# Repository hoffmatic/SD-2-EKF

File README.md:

# SD-2-EKF

Embedded-oriented estimator and airbrake-control scaffold for Project AMBAR.

The code now follows the AMBAR M5 report: a 3-inch test vehicle targeting
3000 ft apogee with +/-100 ft tolerance, autonomous airbrake deployment after
burnout, and live flight-state telemetry.

## What Is Implemented

- 4-state vertical EKF: altitude, vertical velocity, accelerometer bias, and
  barometer bias
- Timestamp validation for asynchronous IMU input
- Barometer innovation gating and Joseph-form covariance update
- Flight phase tracking: pad idle, boost, coast, airbrake active, recovery, fault
- Apogee prediction and bounded airbrake deployment command
- Embedded-friendly interfaces with fixed-size arrays and no heap allocation
- June 2 provisional KiCad pin-map constants in `include/ambar_board_pins.hpp`
- Datasheet-derived device IDs, bus modes, addresses, and register constants in
  `include/ambar_device_constants.hpp`
- Virtual sandboxes for flight behavior, electronics bring-up checks, and
  actuator motion/fault behavior
- RocketPy 1.12.1 trajectory physics using the M5-selected J420R thrust curve
  and a persistent bridge compiled from the production STM32 C estimator and
  flight-controller sources
- Deterministic timestamp/sensor fault injection, synthetic log replay, an
  older 200-trial 1-D safety sandbox, and a production-controller RocketPy
  campaign with per-run CSV output and seeded Latin-hypercube variation
- CTest regression tests and GitHub Actions verification

## Current Status

This is an integration scaffold, not flight-ready software.

The current production-STM32-C RocketPy cross-check fails: the nominal model
predicts 3829 ft AGL passive apogee versus 3379 ft in the June 14 M5 report and
only 42.7 ft/s off the reported 72-inch rail. Closed loop reaches 3327 ft AGL,
about 327 ft above target. These mismatches remain visible until the OpenRocket
configuration, mass properties, and drag data are reconciled.

Before use in flight hardware:

- Calibrate and hardware-qualify the existing sensor, radio, flash, USB, and
  TMC5240 driver paths
- Validate IMU mounting-axis selection, pad reference, and attitude limitations
- Final measured mass properties and drag curves for the RocketPy model
- Calibrate the existing drag-aware embedded predictor against final
  RocketPy/OpenRocket inputs and recorded tests
- Confirm TMC5240 current, speed, travel, homing, load, and fail-safe limits on
  the final mechanism
- Hardware-in-the-loop tests and recorded hardware-log replay
- Verify the existing telemetry/config/log packet paths against the GUI and
  ground station

## Build

If you are new to code or GitHub, start here:
[docs/beginner_quick_start.md](docs/beginner_quick_start.md).

Windows one-command sandbox runner:

```powershell
powershell -ExecutionPolicy Bypass -File .\scripts\run_sandboxes.ps1
```

RocketPy physics simulation:

```powershell
powershell -ExecutionPolicy Bypass -File .\scripts\run_rocketpy_sim.ps1
```

The first RocketPy run creates a local `.venv` and installs the pinned dependency.

Two baseline repeats plus 50 randomized closed-loop runs:

```powershell
powershell -ExecutionPolicy Bypass -File .\scripts\run_monte_carlo.ps1
```

You can also double-click `Run Monte Carlo Simulation.cmd`. Results are written
under `build\monte-carlo\<campaign-id>\`, including `runs.csv`, aggregate
metrics, sensitivity results, and representative profiles. See
[docs/monte_carlo_campaign.md](docs/monte_carlo_campaign.md).
`scripts/validate_monte_carlo_output.py` independently recomputes saved counts,
rates, distributions, joins, worst cases, and snapshot hashes.

Continuous RocketPy replay with one commanded three-rotation actuator sequence
per case is a separate, guarded HIL workflow:

```text
Build & Flash AMBAR Normal.cmd
Build & Flash AMBAR Continuous Test.cmd
Run Continuous HIL Test.cmd
```

The firmware build profile is an explicit flash boundary. `NORMAL` rejects
simulation, HIL override, and arbitrary bench-motion commands.
`CONTINUOUS_HIL` accepts USB trajectory replay and the separately labeled
forced `0 -> 153600 -> 0` TMC ramp-state sequence only after profile,
communications, driver, software-HOME, freshness, and arming checks pass. The
existing PCB is unchanged: PA0/PA1 remain LEDs, and target/`XACTUAL` are not
encoder or endpoint-switch evidence. The launcher requires the mechanism to be
manually fully closed before it declares software HOME once per process. Live evidence is
stored under `%LOCALAPPDATA%\AMBAR\TestRuns`, queried through SQLite, graphed
on a localhost dashboard, and exported to atomic CSV files. See
[docs/continuous_hil_testing.md](docs/continuous_hil_testing.md) and complete
[docs/continuous_hil_commissioning.md](docs/continuous_hil_commissioning.md)
before enabling motor power.

The separate `VARIABLE_HIL` profile closes RocketPy causally around the normal
fractional STM32 controller-to-actuator path and correlated TMC5240 `XACTUAL`
feedback. It rejects the forced FULL/HOME override used by `CONTINUOUS_HIL`,
requires an atomic versioned configuration readback before arming, and stores
hardware-safety and 3,000 ft performance verdicts independently. Because
`XACTUAL` is not an encoder, its results are labeled TMC ramp-state-coupled HIL.
See [docs/variable_hil_testing.md](docs/variable_hil_testing.md).

The guarded launcher is separate from the forced-stroke runner. It does not
open a COM port unless hardware mode, actuator motion, an explicit port, and a
software-HOME acknowledgement are all supplied:

```powershell
powershell -ExecutionPolicy Bypass -File .\scripts\run_variable_hil.ps1 `
  -Hardware -AllowActuatorMotion -Port COMx -Cycles 25
```

The launcher prompts for the exact word `CLOSED` before declaring software
HOME. Do not use the hardware command until the motor-off replay and staged
25/50/75/100% commissioning in the testing guide are complete.

Browser simulation console:

```powershell
powershell -ExecutionPolicy Bypass -File .\scripts\run_simulation_ui.ps1
```

The local dashboard provides Run All/Run Suite controls, adjustable RocketPy
trade-study inputs, scenario tables, interactive altitude/speed/acceleration/
deployment graphs, a production STM32-C phase timeline, CSV/JSON export, source-gap tracking,
and the complete raw terminal output. See
[docs/simulation_ui.md](docs/simulation_ui.md).

```powershell
cmake -S . -B build
cmake --build build
.\build\Debug\rocket_airbrake_ekf.exe
.\build\Debug\sim_flight_sandbox.exe
.\build\Debug\sim_electronics_sandbox.exe
.\build\Debug\sim_actuator_sandbox.exe
.\build\Debug\sim_fault_replay_sandbox.exe
.\build\Debug\sim_monte_carlo_sandbox.exe
.\build\Debug\ambar_core_tests.exe
.\build\Debug\ambar_controller_bridge.exe
.\build\Debug\ambar_stm32_controller_bridge.exe
```

For single-config generators, the executable may be under `build/rocket_airbrake_ekf`.
The sandbox executables may likewise be directly under `build/`.

Direct compiler check, useful on Windows when CMake is not installed:

```powershell
g++ -std=c++17 -Wall -Wextra -Wpedantic -I include src/ambar_airbrake.cpp src/main.cpp -o build\rocket_airbrake_ekf.exe
.\build\rocket_airbrake_ekf.exe
```

Direct sandbox checks:

```powershell
g++ -std=c++17 -Wall -Wextra -Wpedantic -I include src/ambar_airbrake.cpp sim/flight_sandbox.cpp -o build\sim_flight_sandbox.exe
g++ -std=c++17 -Wall -Wextra -Wpedantic -I include sim/electronics_sandbox.cpp -o build\sim_electronics_sandbox.exe
g++ -std=c++17 -Wall -Wextra -Wpedantic -I include sim/actuator_sandbox.cpp -o build\sim_actuator_sandbox.exe
.\build\sim_flight_sandbox.exe
.\build\sim_electronics_sandbox.exe
.\build\sim_actuator_sandbox.exe
```

## Legacy C++ Sensor Interface

The older native C++ scaffold expects vertical acceleration in the launch frame:

```cpp
flightComputer.updateImu(timestamp_s, verticalAcceleration_mps2);
```

The barometer update expects altitude above the launch pad:

```cpp
flightComputer.updateBarometer(barometerAltitudeAgl_m, barometerStdDev_m);
```

The production STM32 firmware instead consumes its configured, pad-referenced
IMU body-axis channel. The main RocketPy campaign now models that current
firmware contract, including attitude projection, while retaining world-vertical
truth as a separate diagnostic.

## Software Architecture

The repository retains an older shared C++ flight-logic scaffold for native
sandboxes. RocketPy and the new Monte Carlo campaign now use a separate bridge
compiled directly from the production STM32 `ambar_ekf.c` and `ambar_flight.c`
sources, preventing controller drift between the board and the main closed-loop
physics study. The browser UI launches programs and displays their reports; it
does not simulate the rocket itself.

See [docs/software_architecture.md](docs/software_architecture.md) for the data
flow, file dependency map, and the intended use case for each executable.

## Current Project Files

- [docs/project_requirements.md](docs/project_requirements.md): AMBAR M5
  requirements mapped to the estimator and controller.
- [docs/project_status.md](docs/project_status.md): implemented, simulated,
  provisional, and future capabilities with the current verification snapshot.
- [docs/hardware_map.md](docs/hardware_map.md): provisional June 2 V3 KiCad
  component and STM32 pin map, including routing maturity.
- [docs/datasheet_integration_notes.md](docs/datasheet_integration_notes.md):
  datasheet facts reflected in firmware constants.
- [docs/simulation_sandboxes.md](docs/simulation_sandboxes.md): project review
  summary and virtual sandbox instructions.
- [docs/simulation_ui.md](docs/simulation_ui.md): browser dashboard startup and
  controls.
- [docs/beginner_quick_start.md](docs/beginner_quick_start.md): plain-English
  instructions for downloading the repo and running the sandboxes on Windows.
- [docs/source_backed_simulation_inputs.md](docs/source_backed_simulation_inputs.md):
  values pulled from the M5 report/KiCad files versus values still treated as
  placeholders.
- [docs/m5_report_data_extract.md](docs/m5_report_data_extract.md): engineering
  values extracted from the June 14 M5 report, their confidence, and conflicts
  with older report material.
- [docs/sensor_architecture.md](docs/sensor_architecture.md): verified separation
  between the airbrake magnetometer and independent recovery GPS.
- [docs/software_architecture.md](docs/software_architecture.md): how the shared
  flight core, simulations, scripts, and browser UI connect.
- [docs/continuous_hil_testing.md](docs/continuous_hil_testing.md): firmware
  profiles, continuous supervisor, datasets, dashboard, and operator controls.
- [docs/continuous_hil_commissioning.md](docs/continuous_hil_commissioning.md):
  unchanged-PCB software-zero procedure, cutoff, staged motion, and 100-cycle
  qualification.
- [docs/variable_hil_testing.md](docs/variable_hil_testing.md): isolated causal
  variable-deployment profile, configuration handshake, timing fault rules,
  calibration gates, and staged 3,000 ft development campaign.
- [docs/simulation_audit.md](docs/simulation_audit.md): engineering review of
  what each simulation proves, current gaps, and recommended next simulations.
- [docs/m5_report_change_guide.md](docs/m5_report_change_guide.md):
  section-by-section advice for manually correcting the Word report.
- [firmware/stm32_airbrake_pcb](firmware/stm32_airbrake_pcb): STM32CubeIDE
  project copy for the Airbrake PCB, including the C EKF port, flash logging,
  radio command parsing, telemetry additions, and bench-gated actuator layer.
- [hardware/airbrake_pcb](hardware/airbrake_pcb): KiCad PCB project and local
  component libraries copied from the Airbrake PCB design folder.
- [hardware/datasheets](hardware/datasheets): local component datasheets used
  for firmware constants, bus assumptions, and safety notes.
- [firmware/rust_controller_reference](firmware/rust_controller_reference):
  standalone Rust controller reference copied from the local PCB folder.
- [tools/arduino_ide_shortcut](tools/arduino_ide_shortcut): readable extraction
  of the local Arduino IDE shortcut metadata.
- [tools/arduino_ground_receiver](tools/arduino_ground_receiver): Arduino/LILYGO
  SX1280 receiver sketch that decodes the STM32 binary EKF telemetry packets.

Older V2 screenshot notes and outdated BOM mismatch notes were removed from the
live repo so GitHub only presents the current working baseline.

## Safety Note

Rocket airbrake software can affect flight stability and recovery outcomes. Treat this
code as experimental until it has been validated with simulation, bench testing,
hardware-in-the-loop testing, and controlled flight data review.

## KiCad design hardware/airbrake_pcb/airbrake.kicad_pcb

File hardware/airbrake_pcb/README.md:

# Airbrake PCB KiCad Project

Source copied from:

```text
C:\Users\hoffm\OneDrive\Desktop\PCBs\PCB\Main Prefab Airbreak PCB\airbrake-PCB
```

This folder contains the live KiCad project files and local component libraries:

- `airbrake.kicad_pro`
- `airbrake.kicad_sch`
- `airbrake.kicad_pcb`
- `fp-lib-table`
- `sym-lib-table`
- `components/`

The local `.history` folder was not uploaded because it contains a nested Git
repository/history cache rather than the active PCB design files.

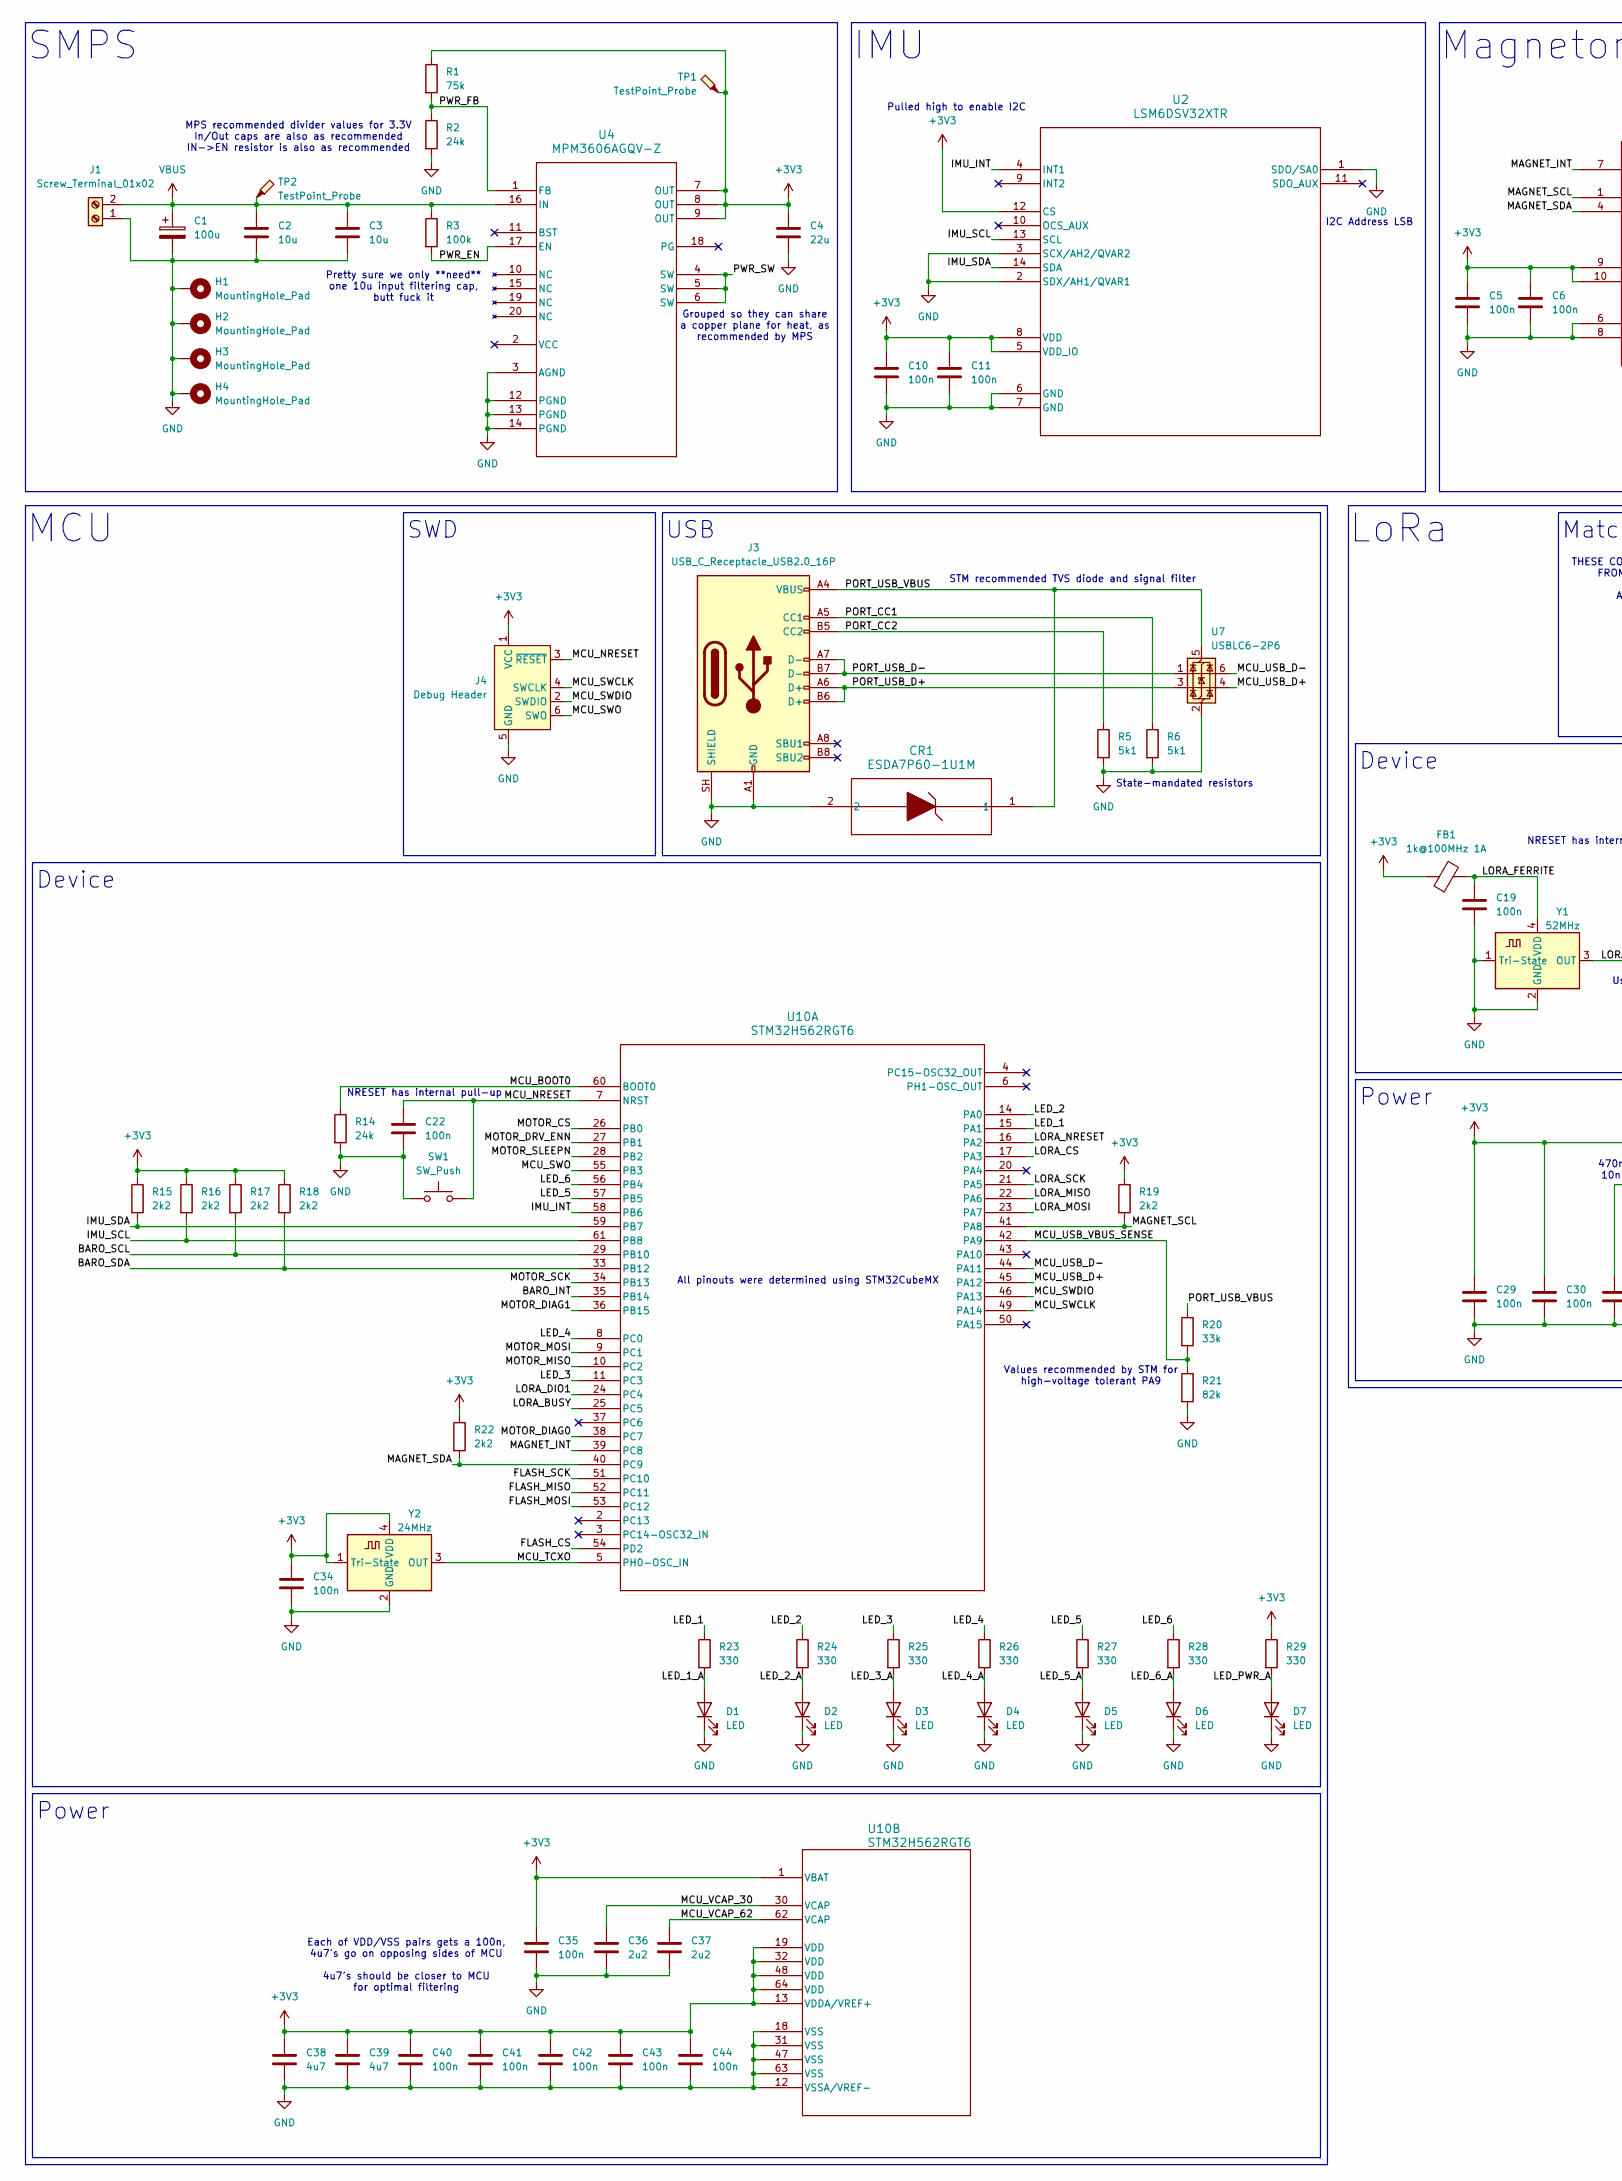
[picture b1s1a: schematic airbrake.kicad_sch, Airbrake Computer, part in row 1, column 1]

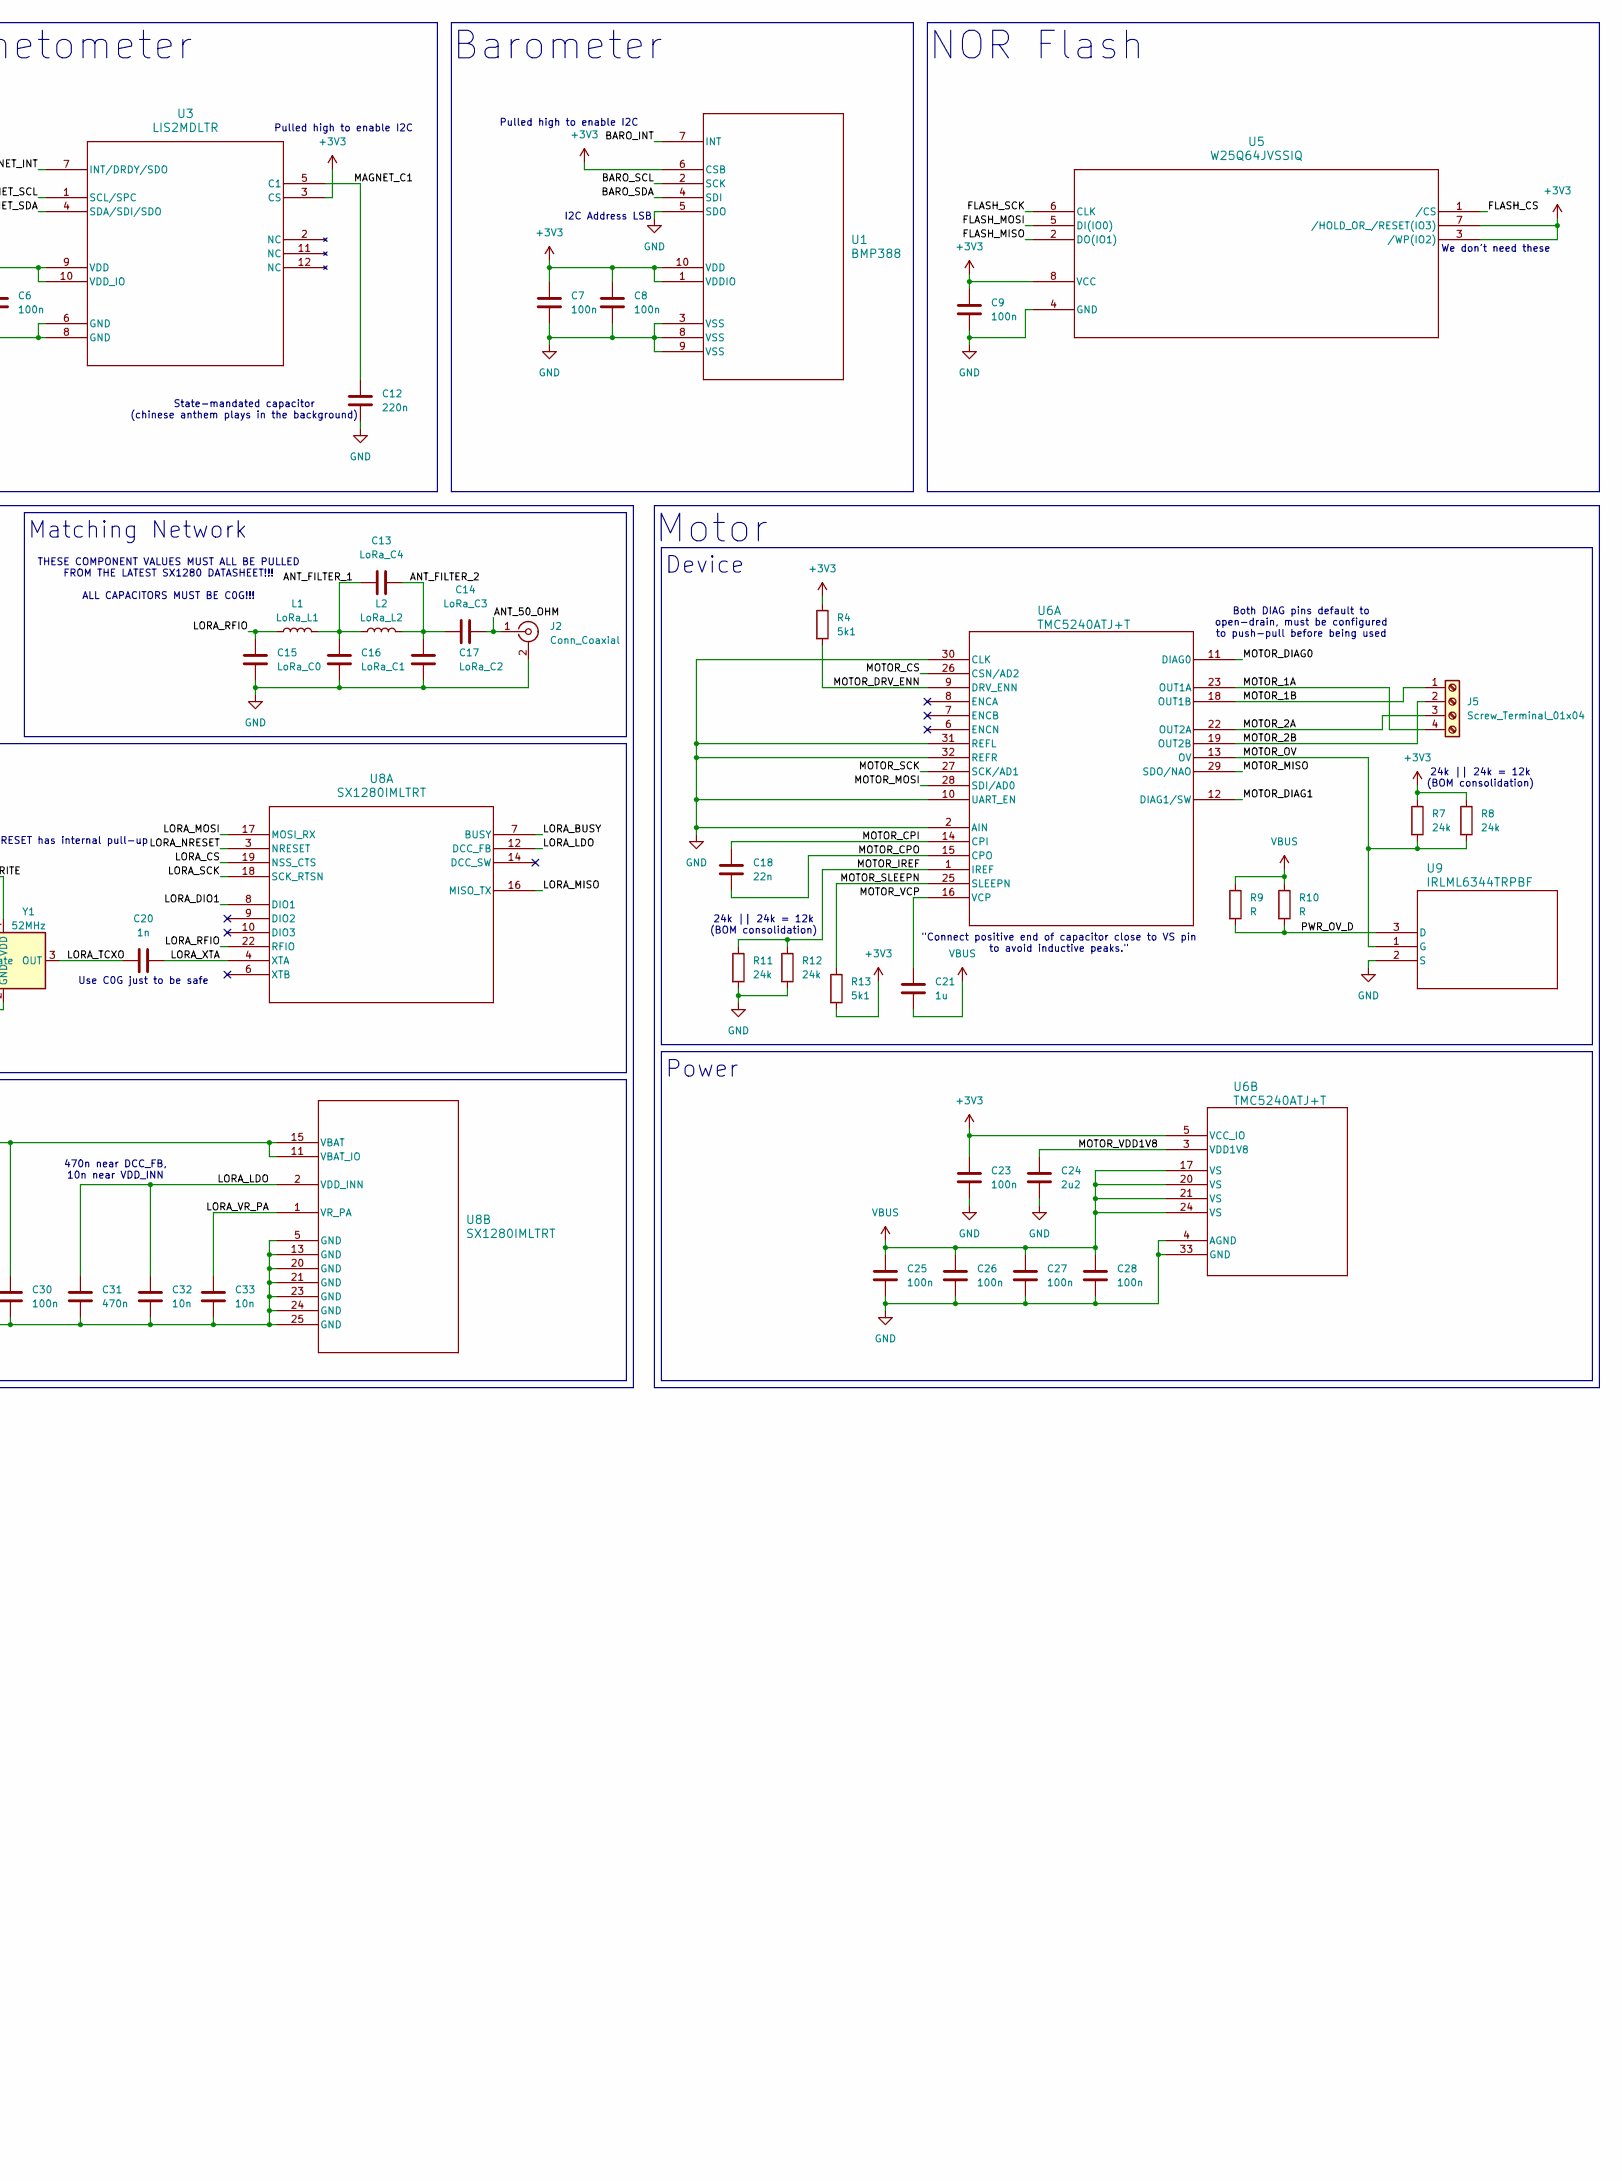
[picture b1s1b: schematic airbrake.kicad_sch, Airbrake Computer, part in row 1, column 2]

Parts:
C1: 100u; CP_Elec_6.3x7.7; LCSC part number C165974
C2, C3: 10u; C_0603_1608Metric; LCSC part number C194427
C4: 22u; C_0603_1608Metric; LCSC part number C29519229
C5, C6, C7, C8, C9, C10, C11, C19, C22, C23, C25, C26, C27, C28, C29, C30, C34, C35, C40, C41, C42, C43, C44: 100n; C_0402_1005Metric; LCSC part number C85858
C12: 220n; C_0402_1005Metric; LCSC part number C5159775
C13: LoRa_C4; C_0402_1005Metric; LCSC part number C76912
C14: LoRa_C3; C_0402_1005Metric; LCSC part number C2941926
C15: LoRa_C0; C_0402_1005Metric; LCSC part number C88902
C16: LoRa_C1; C_0402_1005Metric; LCSC part number C76899
C17: LoRa_C2; C_0402_1005Metric; LCSC part number C76899
C18: 22n; C_0402_1005Metric; LCSC part number C77023
C20: 1n; C_0402_1005Metric; LCSC part number C126493
C21: 1u; C_0402_1005Metric; LCSC part number C1518208
C24, C36, C37: 2u2; C_0402_1005Metric; LCSC part number C237392
C31: 470n; C_0402_1005Metric; LCSC part number C437527
C32, C33: 10n; C_0402_1005Metric; LCSC part number C91601
C38, C39: 4u7; C_0402_1005Metric; LCSC part number C2858031
CR1: ESDA7P60-1U1M; ZDO_1610_STM; LCSC part number C1975146
D1, D2, D3, D4, D5, D6, D7: LED; LED_0402_1005Metric; LCSC part number C25503856
FB1: 1k@100MHz 1A; L_0603_1608Metric; LCSC part number C160982
H1, H2, H3, H4: MountingHole_Pad; MountingHole_2.2mm_M2_Pad_Via
J1: Screw_Terminal_01x02; TerminalBlock_Xinya_XY308-2.54-2P_1x02_P2.54mm_Horizontal; LCSC part number C557685
J2: Conn_Coaxial; U.FL_Hirose_U.FL-R-SMT-1_Vertical; LCSC part number C88374
J3: USB_C_Receptacle_USB2.0_16P; USB_C_Receptacle_GCT_USB4105-xx-A_16P_TopMnt_Horizontal; LCSC part number C5184243
J4: Debug Header; Tag-Connect_TC2030-IDC-NL_2x03_P1.27mm_Vertical
J5: Screw_Terminal_01x04; TerminalBlock_Xinya_XY308-2.54-4P_1x04_P2.54mm_Horizontal; LCSC part number C915913
L1: LoRa_L1; L_0402_1005Metric; LCSC part number C2041661
L2: LoRa_L2; L_0402_1005Metric; LCSC part number C703121
R1: 75k; R_0402_1005Metric; LCSC part number C482299
R2, R7, R8, R11, R12, R14: 24k; R_0402_1005Metric; LCSC part number C295000
R3: 100k; R_0402_1005Metric; LCSC part number C481918
R4, R5, R6, R13: 5k1; R_0402_1005Metric; LCSC part number C2076825
R9, R10: R; R_2512_6332Metric_Pad1.40x3.35mm_HandSolder
R15, R16, R17, R18, R19, R22: 2k2; R_0402_1005Metric; LCSC part number C4202009
R20: 33k; R_0402_1005Metric; LCSC part number C482153
R21: 82k; R_0402_1005Metric; LCSC part number C482240
R23, R24, R25, R26, R27, R28, R29: 330; R_0402_1005Metric; LCSC part number C71626
SW1: SW_Push; SW_SPST_B3U-1000P; LCSC part number C231329
TP1, TP2: TestPoint_Probe; TestPoint_Pad_D2.5mm
U1: BMP388; QFN_BMP388_BOS; LCSC part number C779278
U2: LSM6DSV32XTR; LGA-14L_2p5X3p0X0p86_STM; LCSC part number C22461202
U3: LIS2MDLTR; LGA-12_2X2X1_STM; LCSC part number C919695
U4: MPM3606AGQV-Z; QFN3p0x5p0x1p6_MPM3606A_MNP; LCSC part number C7305220
U5: W25Q64JVSSIQ; SOIC-8_5P28X5P28_WIN-L; LCSC part number C179171
U6: TMC5240ATJ+T; 21-0140_T3255&plus_5C_ADI-L; LCSC part number C7494373
U7: USBLC6-2P6; SOT-666; LCSC part number C15999
U8: SX1280IMLTRT; QFN24_4X4_SEM-L; LCSC part number C125969
U9: IRLML6344TRPBF; IRLML6344TRPBF_INF
U10: STM32H562RGT6; LQFP64-10x10mm_STM; LCSC part number C19711662
Y1: 52MHz; Crystal_SMD_2016-4Pin_2.0x1.6mm; LCSC part number C22434896
Y2: 24MHz; Crystal_SMD_2520-4Pin_2.5x2.0mm; LCSC part number C2451215

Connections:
+3V3: C4.1, C5.1, C6.1, C7.1, C8.1, C9.1, C10.1, C11.1, C23.1, C29.1, C30.1, C34.1, C35.1, C38.1, C39.1, C40.1, C41.1, C42.1, C43.1, C44.1, FB1.1, J4.1 (VCC), R1.1, R4.1, R7.1, R8.1, R13.2, R15.1, R16.1, R17.1, R18.1, R19.1, R22.1, R29.1, TP1.1 (1_1), U1.1 (VDDIO), U1.6 (CSB), U1.10 (VDD), U2.5 (VDD_IO), U2.8 (VDD), U2.12 (CS), U3.3 (CS), U3.9 (VDD), U3.10 (VDD_IO), U4.7 (OUT), U4.8 (OUT), U4.9 (OUT), U5.3 (/WP(IO2)), U5.7 (/HOLD_OR_/RESET(IO3)), U5.8 (VCC), U6.5 (VCC_IO), U8.11 (VBAT_IO), U8.15 (VBAT), U10.1 (VBAT), U10.13 (VDDA/VREF+), U10.19 (VDD), U10.32 (VDD), U10.48 (VDD), U10.64 (VDD), Y2.1 (Tri-State), Y2.4 (VDD)
/ANT_50_OHM: C14.2, J2.1 (In)
/ANT_FILTER_1: C13.1, C16.1, L1.2, L2.1
/ANT_FILTER_2: C13.2, C14.1, C17.1, L2.2
/BARO_INT: U1.7 (INT), U10.35 (PB14)
/BARO_SCL: R17.2, U1.2 (SCK), U10.29 (PB10)
/BARO_SDA: R18.2, U1.4 (SDI), U10.33 (PB12)
/FLASH_CS: U5.1 (/CS), U10.54 (PD2)
/FLASH_MISO: U5.2 (DO(IO1)), U10.52 (PC11)
/FLASH_MOSI: U5.5 (DI(IO0)), U10.53 (PC12)
/FLASH_SCK: U5.6 (CLK), U10.51 (PC10)
/IMU_INT: U2.4 (INT1), U10.58 (PB6)
/IMU_SCL: R16.2, U2.13 (SCL), U10.61 (PB8)
/IMU_SDA: R15.2, U2.14 (SDA), U10.59 (PB7)
/LED_1: R23.1, U10.15 (PA1)
/LED_1_A: D1.2 (A), R23.2
/LED_2: R24.1, U10.14 (PA0)
/LED_2_A: D2.2 (A), R24.2
/LED_3: R25.1, U10.11 (PC3)
/LED_3_A: D3.2 (A), R25.2
/LED_4: R26.1, U10.8 (PC0)
/LED_4_A: D4.2 (A), R26.2
/LED_5: R27.1, U10.57 (PB5)
/LED_5_A: D5.2 (A), R27.2
/LED_6: R28.1, U10.56 (PB4)
/LED_6_A: D6.2 (A), R28.2
/LED_PWR_A: D7.2 (A), R29.2
/LORA_BUSY: U8.7 (BUSY), U10.25 (PC5)
/LORA_CS: U8.19 (NSS_CTS), U10.17 (PA3)
/LORA_DIO1: U8.8 (DIO1), U10.24 (PC4)
/LORA_FERRITE: C19.1, FB1.2, Y1.4 (VDD)
/LORA_LDO: C31.1, C32.1, U8.2 (VDD_INN), U8.12 (DCC_FB)
/LORA_MISO: U8.16 (MISO_TX), U10.22 (PA6)
/LORA_MOSI: U8.17 (MOSI_RX), U10.23 (PA7)
/LORA_NRESET: U8.3 (NRESET), U10.16 (PA2)
/LORA_RFIO: C15.1, L1.1, U8.22 (RFIO)
/LORA_SCK: U8.18 (SCK_RTSN), U10.21 (PA5)
/LORA_TCXO: C20.1, Y1.3 (OUT)
/LORA_VR_PA: C33.1, U8.1 (VR_PA)
/LORA_XTA: C20.2, U8.4 (XTA)
/MAGNET_C1: C12.1, U3.5 (C1)
/MAGNET_INT: U3.7 (INT/DRDY/SDO), U10.39 (PC8)
/MAGNET_SCL: R19.2, U3.1 (SCL/SPC), U10.41 (PA8)
/MAGNET_SDA: R22.2, U3.4 (SDA/SDI/SDO), U10.40 (PC9)
/MCU_BOOT0: R14.1, U10.60 (BOOT0)
/MCU_NRESET: C22.1, J4.3 (~RESET), SW1.2, U10.7 (NRST)
/MCU_SWCLK: J4.4 (SWCLK), U10.49 (PA14)
/MCU_SWDIO: J4.2 (SWDIO), U10.46 (PA13)
/MCU_SWO: J4.6 (SWO), U10.55 (PB3)
/MCU_TCXO: U10.5 (PH0-OSC_IN), Y2.3 (OUT)
/MCU_USB_D+: U7.4 (I/O2), U10.45 (PA12)
/MCU_USB_D-: U7.6 (I/O1), U10.44 (PA11)
/MCU_USB_VBUS_SENSE: R20.2, R21.1, U10.42 (PA9)
/MCU_VCAP_30: C36.1, U10.30 (VCAP)
/MCU_VCAP_62: C37.1, U10.62 (VCAP)
/MOTOR_1A: J5.4, U6.23 (OUT1A)
/MOTOR_1B: J5.1, U6.18 (OUT1B)
/MOTOR_2A: J5.3, U6.22 (OUT2A)
/MOTOR_2B: J5.2, U6.19 (OUT2B)
/MOTOR_CPI: C18.1, U6.14 (CPI)
/MOTOR_CPO: C18.2, U6.15 (CPO)
/MOTOR_CS: U6.26 (CSN/AD2), U10.26 (PB0)
/MOTOR_DIAG0: U6.11 (DIAG0), U10.38 (PC7)
/MOTOR_DIAG1: U6.12 (DIAG1/SW), U10.36 (PB15)
/MOTOR_DRV_ENN: R4.2, U6.9 (DRV_ENN), U10.27 (PB1)
/MOTOR_IREF: R11.1, R12.1, U6.1 (IREF)
/MOTOR_MISO: U6.29 (SDO/NAO), U10.10 (PC2)
/MOTOR_MOSI: U6.28 (SDI/AD0), U10.9 (PC1)
/MOTOR_OV: R7.2, R8.2, U6.13 (OV), U9.1 (G)
/MOTOR_SCK: U6.27 (SCK/AD1), U10.34 (PB13)
/MOTOR_SLEEPN: R13.1, U6.25 (SLEEPN), U10.28 (PB2)
/MOTOR_VCP: C21.1, U6.16 (VCP)
/MOTOR_VDD1V8: C24.1, U6.3 (VDD1V8)
/PORT_CC1: J3.A5 (CC1), R6.1
/PORT_CC2: J3.B5 (CC2), R5.1
/PORT_USB_D+: J3.A6 (D+), J3.B6 (D+), U7.3 (I/O2)
/PORT_USB_D-: J3.A7 (D-), J3.B7 (D-), U7.1 (I/O1)
/PORT_USB_VBUS: CR1.1, J3.A4 (VBUS), J3.A9 (VBUS), J3.B4 (VBUS), J3.B9 (VBUS), R20.1, U7.5 (VBUS)
/PWR_EN: R3.2, U4.17 (EN)
/PWR_FB: R1.2, R2.1, U4.1 (FB)
/PWR_OV_D: R9.2, R10.2, U9.3 (D)
/PWR_SW: U4.4 (SW), U4.5 (SW), U4.6 (SW)
GND: C1.2, C2.2, C3.2, C4.2, C5.2, C6.2, C7.2, C8.2, C9.2, C10.2, C11.2, C12.2, C15.2, C16.2, C17.2, C19.2, C22.2, C23.2, C24.2, C25.2, C26.2, C27.2, C28.2, C29.2, C30.2, C31.2, C32.2, C33.2, C34.2, C35.2, C36.2, C37.2, C38.2, C39.2, C40.2, C41.2, C42.2, C43.2, C44.2, CR1.2, D1.1 (K), D2.1 (K), D3.1 (K), D4.1 (K), D5.1 (K), D6.1 (K), D7.1 (K), H1.1 (1_1), H2.1 (1_1), H3.1 (1_1), H4.1 (1_1), J1.1, J2.2 (Ext), J3.A1 (GND), J3.A12 (GND), J3.B1 (GND), J3.B12 (GND), J3.SH (SHIELD), J4.5 (GND), R2.2, R5.2, R6.2, R11.2, R12.2, R14.2, R21.2, SW1.1, U1.3 (VSS), U1.5 (SDO), U1.8 (VSS), U1.9 (VSS), U2.1 (SDO/SA0), U2.2 (SDX/AH1/QVAR1), U2.3 (SCX/AH2/QVAR2), U2.6 (GND), U2.7 (GND), U3.6 (GND), U3.8 (GND), U4.3 (AGND), U4.12 (PGND), U4.13 (PGND), U4.14 (PGND), U5.4 (GND), U6.2 (AIN), U6.4 (AGND), U6.10 (UART_EN), U6.30 (CLK), U6.31 (REFL), U6.32 (REFR), U6.33 (GND), U7.2 (GND), U8.5 (GND), U8.13 (GND), U8.20 (GND), U8.21 (GND), U8.23 (GND), U8.24 (GND), U8.25 (GND), U9.2 (S), U10.12 (VSSA/VREF-), U10.18 (VSS), U10.31 (VSS), U10.47 (VSS), U10.63 (VSS), Y1.1 (Tri-State), Y1.2 (GND), Y2.2 (GND)
VBUS: C1.1, C2.1, C3.1, C21.2, C25.1, C26.1, C27.1, C28.1, J1.2, R3.1, R9.1, R10.1, TP2.1 (1_1), U4.16 (IN), U6.17 (VS), U6.20 (VS), U6.21 (VS), U6.24 (VS)

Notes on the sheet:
MCU
NRESET has internal pull-up
Pulled high to enable I2C
Each of VDD/VSS pairs gets a 100n, 4u7's go on opposing sides of MCU 4u7's should be closer to MCU for optimal filtering
Values recommended by STM for high-voltage tolerant PA9
State-mandated resistors
All pinouts were determined using STM32CubeMX
Motor
SMPS
Power
Device
I2C Address LSB
Use C0G just to be safe
Barometer
Matching Network
470n near DCC_FB, 10n near VDD_INN
NOR Flash
24k || 24k = 12k (BOM consolidation)
Both DIAG pins default to open-drain, must be configured to push-pull before being used
SWD
LoRa
MPS recommended divider values for 3.3V In/Out caps are also as recommended IN->EN resistor is also as recommended
IMU
Grouped so they can share a copper plane for heat, as recommended by MPS
Magnetometer
"Connect positive end of capacitor close to VS pin to avoid inductive peaks."
USB
State-mandated capacitor (chinese anthem plays in the background)
THESE COMPONENT VALUES MUST ALL BE PULLED FROM THE LATEST SX1280 DATASHEET!!! ALL CAPACITORS MUST BE C0G!!!
We don't need these
Pretty sure we only **need** one 10u input filtering cap, butt fuck it
STM recommended TVS diode and signal filter

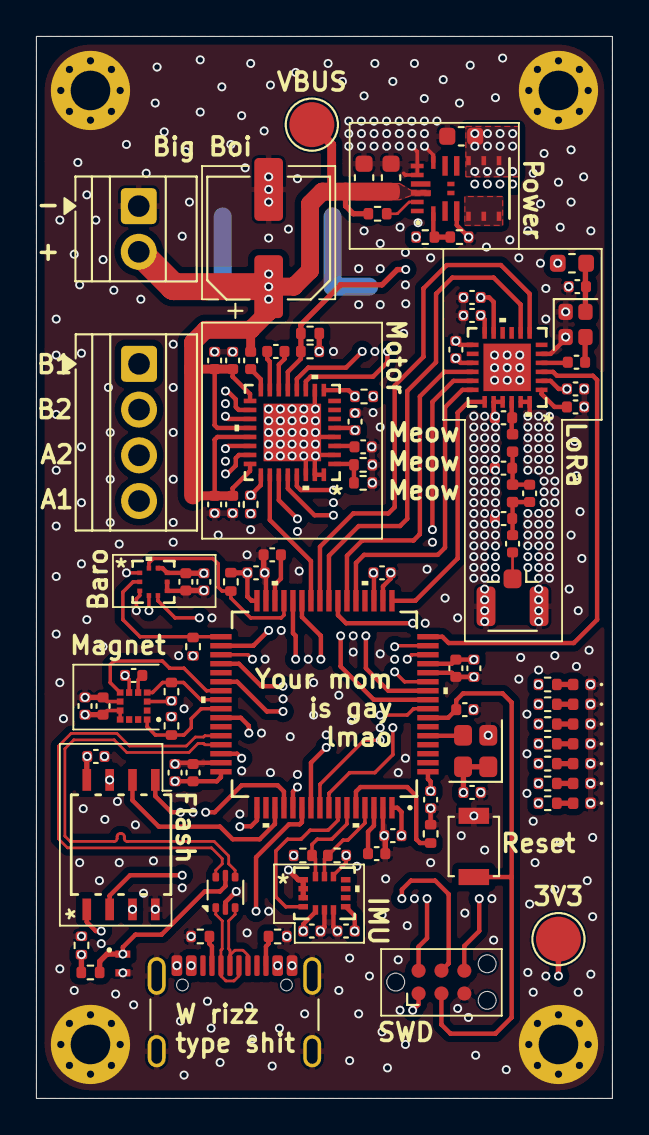
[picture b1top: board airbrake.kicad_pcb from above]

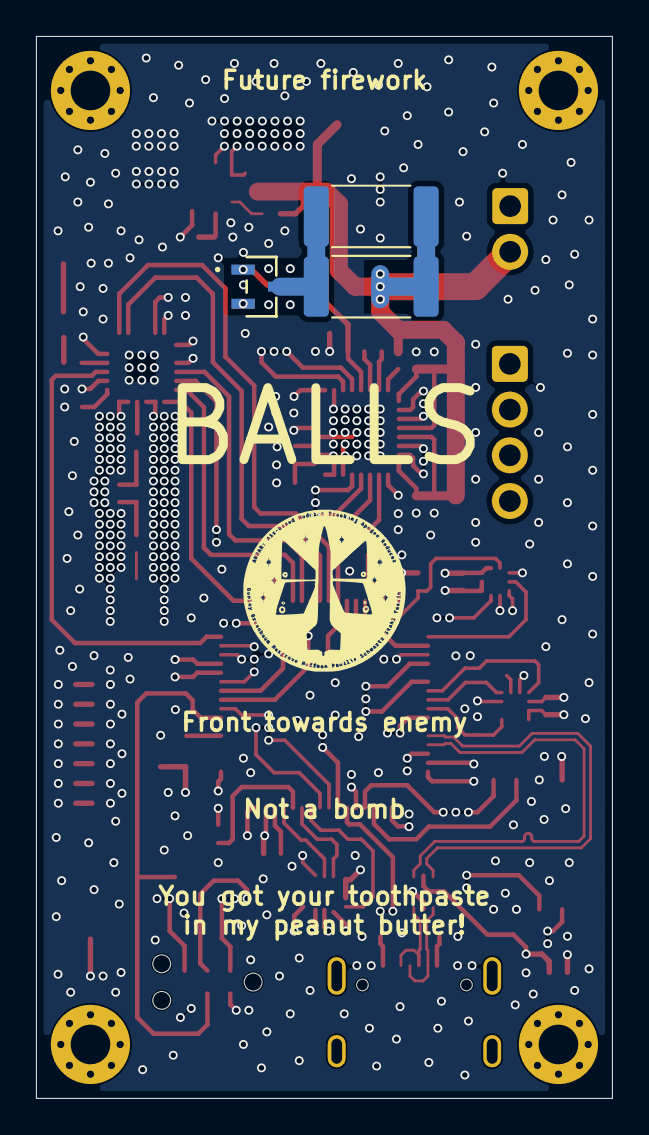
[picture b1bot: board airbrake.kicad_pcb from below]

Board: 6 copper layers, 32.0 x 59.0 mm, 108 parts (3 on the bottom side), 84 nets.

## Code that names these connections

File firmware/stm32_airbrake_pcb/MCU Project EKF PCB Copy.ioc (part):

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Mcu.Name=STM32H562RGTx
Mcu.Package=LQFP64
Mcu.UserName=STM32H562RGTx
PA0.GPIOParameters=GPIO_Speed,GPIO_Label
PA0.GPIO_Label=LED_2
PA0.GPIO_Speed=GPIO_SPEED_FREQ_LOW
PA0.Signal=GPIO_Output
PA1.GPIOParameters=GPIO_Label
PA1.GPIO_Label=LED_1
PA1.Signal=GPIO_Output
PA11.Mode=Device
PA11.Signal=USB_DM
PA12.Mode=Device
PA12.Signal=USB_DP
PA13(JTMS/SWDIO).Mode=Trace_Asynchronous_SW
PA13(JTMS/SWDIO).Signal=DEBUG_JTMS-SWDIO
PA14(JTCK/SWCLK).Mode=Trace_Asynchronous_SW
PA14(JTCK/SWCLK).Signal=DEBUG_JTCK-SWCLK
PA2.GPIOParameters=GPIO_Label
PA2.GPIO_Label=LORA_NRESET
PA2.Signal=GPIO_Output
PA3.GPIOParameters=PinState,GPIO_Label
PA3.GPIO_Label=LORA_CS
PA3.PinState=GPIO_PIN_SET
PA3.Signal=GPIO_Output
PA5.Mode=Full_Duplex_Master
PA5.Signal=SPI1_SCK
PA6.Mode=Full_Duplex_Master
PA6.Signal=SPI1_MISO
PA7.Mode=Full_Duplex_Master
PA7.Signal=SPI1_MOSI
PA8.Mode=I2C
PA8.Signal=I2C3_SCL
PA9.GPIOParameters=GPIO_Label
PA9.GPIO_Label=USB_SENSE
PA9.Signal=GPIO_Input
PB0.GPIOParameters=PinState,GPIO_Label
PB0.GPIO_Label=MOTOR_CS
PB0.PinState=GPIO_PIN_SET
PB0.Signal=GPIO_Output
PB1.GPIOParameters=PinState,GPIO_Label
PB1.GPIO_Label=MOTOR_DRV_ENN
PB1.PinState=GPIO_PIN_SET
PB1.Signal=GPIO_Output
PB10.Mode=I2C
PB10.Signal=I2C2_SCL
PB12.Mode=I2C
PB12.Signal=I2C2_SDA
PB13.Mode=Full_Duplex_Master
PB13.Signal=SPI2_SCK
PB14.GPIOParameters=GPIO_Label
PB14.GPIO_Label=BARO_INT
PB14.Signal=GPXTI14
PB15.GPIOParameters=GPIO_Label
PB15.GPIO_Label=MOTOR_DIAG1
PB15.Signal=GPXTI15
PB2.GPIOParameters=PinState,GPIO_Label
PB2.GPIO_Label=MOTOR_SLEEPN
PB2.PinState=GPIO_PIN_SET
PB2.Signal=GPIO_Output
PB3(JTDO/TRACESWO).Mode=Trace_Asynchronous_SW
PB3(JTDO/TRACESWO).Signal=DEBUG_JTDO-SWO
PB4(NJTRST).GPIOParameters=GPIO_Label
PB4(NJTRST).GPIO_Label=LED_6
PB4(NJTRST).Signal=GPIO_Output
PB5.GPIOParameters=GPIO_Label
PB5.GPIO_Label=LED_5
PB5.Signal=GPIO_Output
PB6.GPIOParameters=GPIO_Label
PB6.GPIO_Label=I2C1_INT
PB6.Signal=GPXTI6
PB7.Mode=I2C
PB7.Signal=I2C1_SDA
PB8.Mode=I2C
PB8.Signal=I2C1_SCL
PC0.GPIOParameters=GPIO_Label
PC0.GPIO_Label=LED_4
PC0.Signal=GPIO_Output
PC1.Mode=Full_Duplex_Master
PC1.Signal=SPI2_MOSI
PC10.Mode=Full_Duplex_Master
PC10.Signal=SPI3_SCK
PC11.Mode=Full_Duplex_Master
PC11.Signal=SPI3_MISO
PC12.Mode=Full_Duplex_Master
PC12.Signal=SPI3_MOSI
PC2.Mode=Full_Duplex_Master
PC2.Signal=SPI2_MISO
PC3.GPIOParameters=GPIO_Label
PC3.GPIO_Label=LED_3
PC3.Signal=GPIO_Output
PC4.GPIOParameters=GPIO_Label
PC4.GPIO_Label=LORA_DIO1
PC4.Signal=GPXTI4
PC5.GPIOParameters=GPIO_Label
PC5.GPIO_Label=LORA_BUSY
PC5.Signal=GPXTI5
PC7.GPIOParameters=GPIO_Label
PC7.GPIO_Label=MOTOR_DIAG0
PC7.Signal=GPXTI7
PC8.GPIOParameters=GPIO_Label
PC8.GPIO_Label=I2C3_INT
PC8.Signal=GPXTI8
PC9.Mode=I2C
PC9.Signal=I2C3_SDA
PD2.GPIOParameters=PinState,GPIO_Label
PD2.GPIO_Label=FLASH_CS
PD2.PinState=GPIO_PIN_SET
PD2.Signal=GPIO_Output
PH0-OSC_IN(PH0).Mode=HSE-DIG-External-Clock-Source
PH0-OSC_IN(PH0).Signal=RCC_OSC_IN
RCC.HSE_VALUE=24000000
RCC.SYSCLKFreq_VALUE=250000000
RCC.SYSCLKSource=RCC_SYSCLKSOURCE_PLLCLK
board=custom

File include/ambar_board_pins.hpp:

#pragma once

// Architecture role: hardware-to-firmware naming boundary for the V3 PCB.
// Desktop code uses these constants for compile-time and electronics-sandbox
// checks. A future STM32 board-support package should translate them into HAL
// or LL GPIO configuration without placing MCU details in the flight logic.

#include <cstdint>

namespace ambar::board {

// Small pin-description types keep the hardware map independent from any one
// STM32 library. The final firmware can translate these into HAL/LL GPIO names.
enum class GpioPort : std::uint8_t {
    A,
    B,
    C,
    D,
    H
};

// A single physical MCU pin, for example PB8 or PA5.
struct GpioPin {
    GpioPort port;
    std::uint8_t pin;
};

// I2C sensors in this design each have clock, data, and a data-ready/interrupt
// line. Keeping interrupt with the bus avoids losing that relationship later.
struct I2cPins {
    GpioPin scl;
    GpioPin sda;
    GpioPin interrupt;
};

// Generic 4-wire SPI wiring used by radio, flash, and motor driver.
struct SpiPins {
    GpioPin sck;
    GpioPin miso;
    GpioPin mosi;
    GpioPin chipSelect;
};

// SX1280 needs SPI plus explicit reset, DIO1 interrupt, and BUSY handshake.
struct Sx1280Pins {
    SpiPins spi;
    GpioPin reset;
    GpioPin dio1;
    GpioPin busy;
};

// TMC5240 is controlled over SPI, but enable/sleep/diagnostic pins are just as
// important for safe actuator bring-up and fault handling.
struct Tmc5240Pins {
    SpiPins spi;
    GpioPin driverEnableN;
    GpioPin sleepN;
    GpioPin diag0;
    GpioPin diag1;
};

// Helpers make the pin table below readable and constexpr-friendly.
inline constexpr GpioPin pinA(std::uint8_t pin) {
    return {GpioPort::A, pin};
}

inline constexpr GpioPin pinB(std::uint8_t pin) {
    return {GpioPort::B, pin};
}

inline constexpr GpioPin pinC(std::uint8_t pin) {
    return {GpioPort::C, pin};
}

inline constexpr GpioPin pinD(std::uint8_t pin) {
    return {GpioPort::D, pin};
}

inline constexpr GpioPin pinH(std::uint8_t pin) {
    return {GpioPort::H, pin};
}

// LSM6DSV32X IMU bus from the June 1 KiCad design. This is the high-rate sensor
// that will feed vertical acceleration after body-axis alignment.
inline constexpr I2cPins kImuPins{
    pinB(8), // IMU_SCL
    pinB(7), // IMU_SDA
    pinB(6)  // IMU_INT
};

// BMP388 barometer bus. This is the slower altitude correction path for the EKF.
inline constexpr I2cPins kBarometerPins{
    pinB(10), // BARO_SCL
    pinB(12), // BARO_SDA
    pinB(14)  // BARO_INT
};

// LIS2MDL magnetometer bus. It is not required for the current vertical EKF but
// is useful for later attitude/alignment checks and telemetry health.
inline constexpr I2cPins kMagnetometerPins{
    pinA(8), // MAGNET_SCL
    pinC(9), // MAGNET_SDA
    pinC(8)  // MAGNET_INT
};

// SX1280 radio used for telemetry/configuration. Firmware must obey BUSY before
// sending commands.
inline constexpr Sx1280Pins kRadioPins{
    {
        pinA(5), // LORA_SCK
        pinA(6), // LORA_MISO
        pinA(7), // LORA_MOSI
        pinA(3)  // LORA_CS
    },
    pinA(2), // LORA_NRESET
    pinC(4), // LORA_DIO1
    pinC(5)  // LORA_BUSY
};

// W25Q64 SPI flash for future flight-log storage.
inline constexpr SpiPins kFlashPins{
    pinC(10), // FLASH_SCK
    pinC(11), // FLASH_MISO
    pinC(12), // FLASH_MOSI
    pinD(2)   // FLASH_CS
};

// TMC5240 actuator driver/controller for the stepper-based airbrake mechanism.
inline constexpr Tmc5240Pins kMotorDriverPins{
    {
        pinB(13), // MOTOR_SCK
        pinC(2),  // MOTOR_MISO
        pinC(1),  // MOTOR_MOSI
        pinB(0)   // MOTOR_CS
    },
    pinB(1),  // MOTOR_DRV_ENN
    pinB(2),  // MOTOR_SLEEPN
    pinC(7),  // MOTOR_DIAG0
    pinB(15)  // MOTOR_DIAG1
};

// User/status LEDs. These are handy for boot stage, sensor checks, arming state,
// and fault display when USB/telemetry is not connected.
inline constexpr GpioPin kLedPins[] = {
    pinA(1), // LED_1
    pinA(0), // LED_2
    pinC(3), // LED_3
    pinC(0), // LED_4
    pinB(5), // LED_5
    pinB(4)  // LED_6
};

// USB/debug pins are listed here so board bring-up code can keep them reserved.
inline constexpr GpioPin kUsbVbusSensePin = pinA(9);
inline constexpr GpioPin kSwdioPin = pinA(13);
inline constexpr GpioPin kSwclkPin = pinA(14);
inline constexpr GpioPin kSwoPin = pinB(3);

// PH0 is named MCU_TCXO in KiCad. Confirm final use before enabling it in the
// radio driver.
inline constexpr GpioPin kTcxoPin = pinH(0);

} // namespace ambar::board

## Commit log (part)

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2026-05-22 Initial rocket airbrake EKF scaffold
2026-05-22 Adapt estimator for AMBAR airbrake control
2026-05-22 Document AMBAR BOM hardware interfaces
2026-05-22 Add V2 schematic reference notes
2026-05-30 Add V3 KiCad hardware map
2026-06-01 Update hardware map for June 1 PCB
2026-06-01 Add datasheet-derived device constants
2026-06-01 Organize repository around current AMBAR baseline
2026-06-01 Add explanatory code comments
2026-06-04 Add virtual simulation sandboxes
2026-06-04 Add beginner sandbox quick start
2026-06-04 Clarify sandbox pass fail logging
2026-06-04 Pull M3 requirements into simulations
2026-06-05 Tighten sandbox sanity checks
2026-06-12 Add simulation console UI
2026-06-12 Integrate RocketPy physics simulation
2026-06-14 Document software architecture and clean repository metadata
2026-06-14 Audit and strengthen simulation checks
2026-06-14 Integrate June 14 M5 report data
2026-06-14 Add adjustable RocketPy simulation inputs
2026-06-14 Strengthen AMBAR verification and project status
2026-06-15 Add validated flight-data graphs
